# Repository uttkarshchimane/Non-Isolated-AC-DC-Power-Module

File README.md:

# ⚡ Non-Isolated AC-DC Power Supply (230V AC to 5V DC)

---

## ⚙️ What I Built

A **capacitive dropper-based AC-DC power supply** designed to step down **230V AC** and provide a regulated low-voltage DC output (**~5V, low current**).

---

## 🚀 Overview

This design eliminates bulky transformers by using a **reactive impedance (capacitor)** to efficiently drop voltage.

It includes:

* Capacitive voltage dropper
* Full-wave bridge rectifier
* Filtering stage
* Zener-based regulation
* Linear voltage regulator for stable 5V output

---

## 📷 Project Preview

---

## 🧠 Design Architecture (Key Stages)

🔌 **Input Stage**

* 230V AC input via screw terminal
* Capacitor (C4) acts as voltage dropper
* Resistor (R3) for inrush current limiting

🔄 **Rectification**

* Bridge rectifier using **4× 1N4007 diodes**

🔋 **Filtering**

* Bulk capacitor (**1000µF**) smooths DC
* Small capacitor (**0.1µF**) for noise suppression

⚖️ **Regulation**

* Zener diodes stabilize intermediate voltage
* **7805 linear regulator** provides steady 5V output

🔌 **Output Stage**

* 470µF capacitor for ripple reduction
* LED indicator for power status

---

## 📌 Key Takeaways

✔ Compact and cost-effective design
✔ Eliminates bulky transformers

❌ Non-isolated → serious safety limitations

⚠️ Suitable only for **low-power, controlled environments** due to direct mains interaction

---

## 🧩 PCB Design Insights

* Maintained separation between high-voltage and low-voltage sections
* Optimized component placement for shorter trace paths
* Considered spacing constraints for safer operation
* Used 3D visualization to validate layout decisions

---

## ⚠️ Safety Note

This is a **non-isolated power supply**:

* Output is directly referenced to mains
* Risk of electric shock is high
* Not suitable for open-use or human interaction

👉 Use only in **enclosed, insulated systems**

---

## 🧪 Applications

* Low-power embedded systems
* IoT nodes
* Indicator / control circuits

---

## ⚠️ Limitations

- No electrical isolation from mains  
- Limited current capability  
- Poor regulation under varying load  
- Not suitable for high-power applications  

---

## 🚀 Future Improvements

- Replace with isolated SMPS design  
- Add fuse and MOV for protection  
- Improve thermal handling  
- Compact SMD version  

---

## 🛠 Tools Used

* KiCad (Schematic + PCB Design + 3D visualization)

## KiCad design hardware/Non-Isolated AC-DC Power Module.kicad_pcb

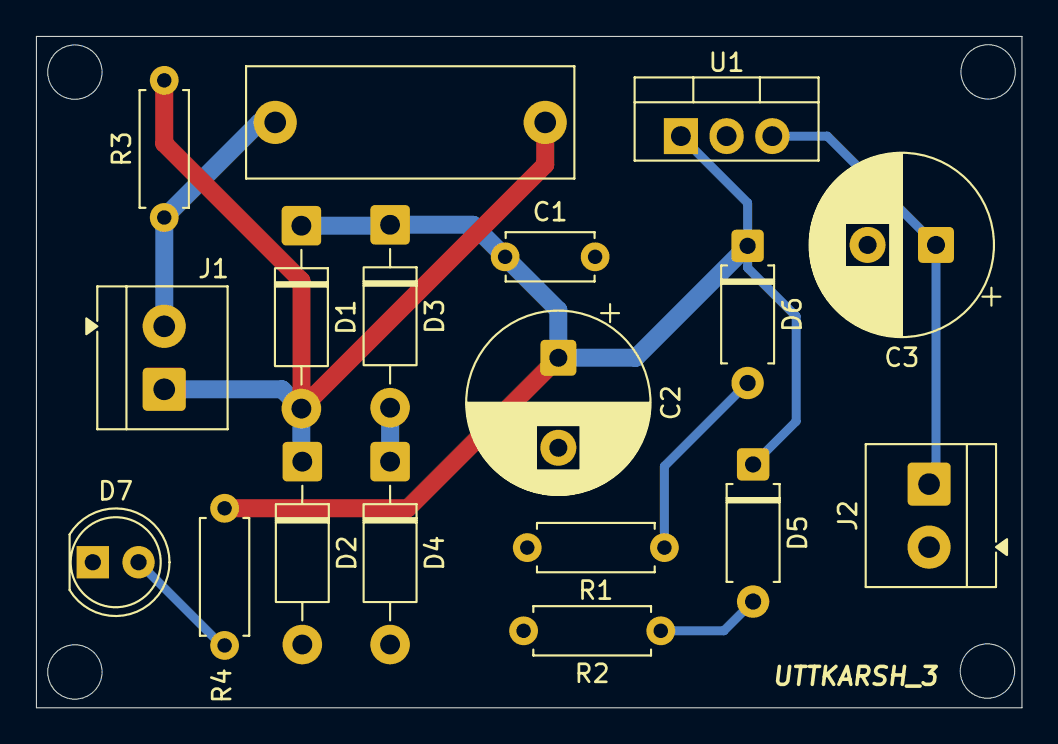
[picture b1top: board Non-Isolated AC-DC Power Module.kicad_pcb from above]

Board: 2 copper layers, 54.8 x 37.3 mm, 18 parts (0 on the bottom side), 9 nets.

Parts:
C1: 0.1uf; C_Disc_D4.7mm_W2.5mm_P5.00mm
C2: 1000uf; CP_Radial_D10.0mm_P5.00mm
C3: 470uf; CP_Radial_D10.0mm_P3.80mm
C4: 225K/2.2uf; C_Rect_L18.0mm_W6.0mm_P15.00mm_FKS3_FKP3
D1, D2, D3, D4: 1N4007; D_DO-41_SOD81_P10.16mm_Horizontal
D5, D6: D_Zener; D_A-405_P7.62mm_Horizontal
D7: LED; LED_D5.0mm
J1, J2: Screw_Terminal_01x02; TerminalBlock_4Ucon_1x02_P3.50mm_Horizontal
R1, R2: 20K; R_Axial_DIN0207_L6.3mm_D2.5mm_P7.62mm_Horizontal
R3: 1M; R_Axial_DIN0207_L6.3mm_D2.5mm_P7.62mm_Horizontal
R4: 2.2K; R_Axial_DIN0207_L6.3mm_D2.5mm_P7.62mm_Horizontal
U1: LM7805_TO220; TO-220-3_Vertical

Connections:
/5V: C3.1, J2.1, U1.3 (VO)
GND: C1.2, C2.2, C3.2, D2.2 (A), D4.2 (A), D7.1 (K), J2.2, R1.2, R2.2, U1.2 (GND)
unnamed: C4.2, D1.2 (A), D2.1 (K), J1.1, R3.2
unnamed: C1.1, C2.1, D1.1 (K), D3.1 (K), D5.1 (K), D6.1 (K), R4.1, U1.1 (VI)
unnamed: D3.2 (A), D4.1 (K)
unnamed: D5.2 (A), R2.1
unnamed: D6.2 (A), R1.1
unnamed: D7.2 (A), R4.2
unnamed: C4.1, J1.2, R3.1

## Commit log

2026-05-06 Initial commit - Non-Isolated AC-DC Power Module With Documentation And Design Files
2026-05-06 Reorder schematic image in README
2026-05-30 Update README.md
    Removed testing and results section from README.
